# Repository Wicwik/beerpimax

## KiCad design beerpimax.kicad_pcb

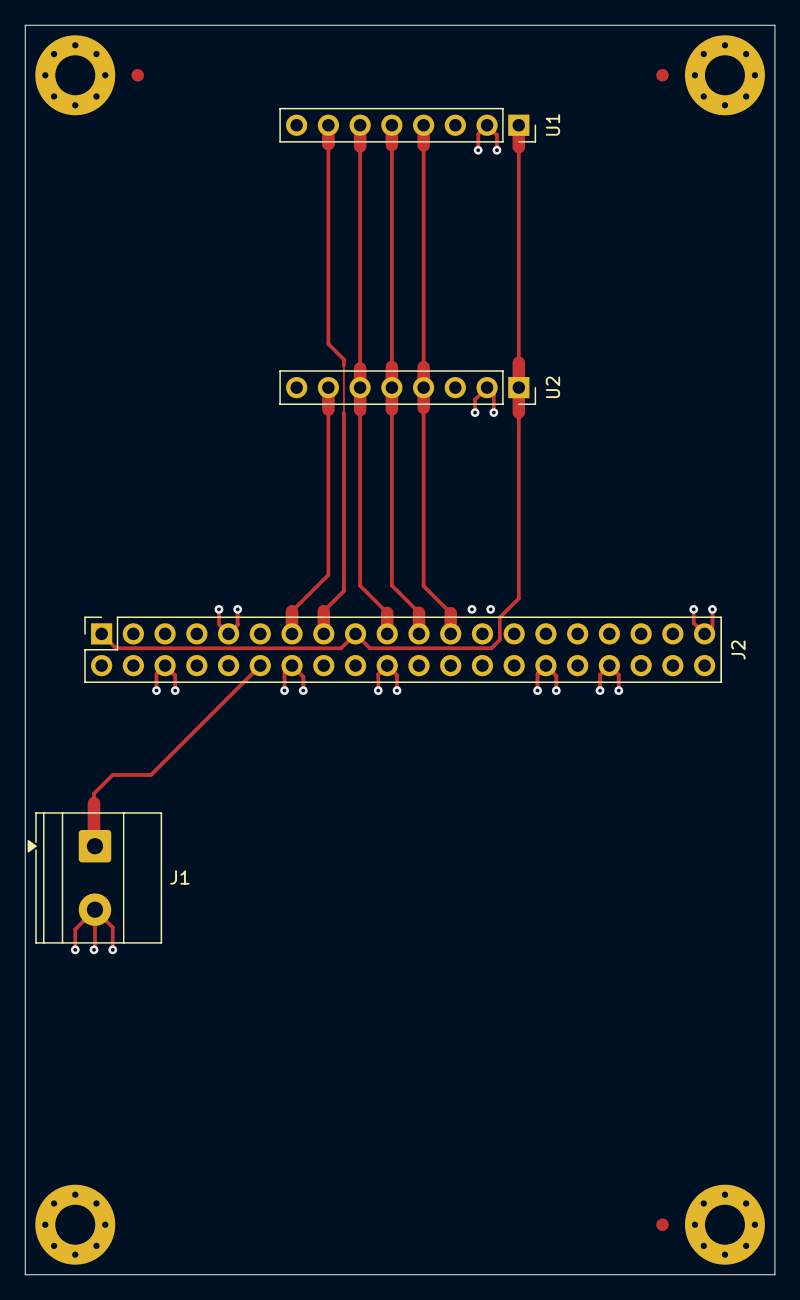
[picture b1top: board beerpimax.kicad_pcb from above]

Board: 2 copper layers, 60.0 x 100.0 mm, 11 parts (0 on the bottom side), 8 nets.

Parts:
FID1, FID2, FID3: Fiducial; Fiducial_1mm_Mask2mm
J1: SSR Terminal; TerminalBlock_Phoenix_MKDS-1,5-2-5.08_1x02_P5.08mm_Horizont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
J2: Raspberry_Pi_2_3; PinSocket_2x20_P2.54mm_Vertical
MH1, MH2, MH3, MH4: M3; MountingHole_3.2mm_M3_Pad_Via
U1, U2: MAX31865; PinSocket_1x08_P2.54mm_Vertical

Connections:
+3V3: J2.1 (3V3), J2.17 (3V3), U1.1 (VIN), U2.1 (VIN)
/SPIGPIO7: J2.15 (GPIO22), U1.7 (CS)
/SPIGPIO8: J2.13 (GPIO27), U2.7 (CS)
/SPIMISO: J2.21 (MISO0/GPIO9), U1.5 (SDO), U2.5 (SDO)
/SPIMOSI: J2.19 (MOSI0/GPIO10), U1.6 (SDI), U2.6 (SDI)
/SPISCLK: J2.23 (SCLK0/GPIO11), U1.4 (CLK), U2.4 (CLK)
/SSRGPIO18: J1.1, J2.12 (GPIO18/PWM0)
GND: J1.2, J2.6 (GND), J2.9 (GND), J2.14 (GND), J2.20 (GND), J2.25 (GND), J2.30 (GND), J2.34 (GND), J2.39 (GND), MH1.1 (1_1), MH2.1 (1_1), MH3.1 (1_1), MH4.1 (1_1), U1.2 (GND), U2.2 (GND)

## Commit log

2026-05-17 board layout done
2026-05-18 finished pcb design?
2026-05-18 minor changes
